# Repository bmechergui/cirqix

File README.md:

# Cirqix.ai — AI PCB Design Agent

> **From idea to manufacturable PCB, autonomously**

Cirqix is a cloud SaaS for PCB design powered by natural language. Describe your circuit, the AI agent generates a DRC-clean PCB and exports Gerbers/BOM for review and manual manufacturer submission.

---

## What it does

```
User prompt → 8 AI Agents → Schematic → ERC → Footprints → PCB → Placement → Routing → DRC → Gerbers/BOM
```

1. **Describe** — type your circuit in natural language
2. **Design** — 8 specialized AI agents create schematic, resolve footprints, place components, route traces, fix all DRC violations
3. **Review** — visualize schematic + PCB in KiCanvas, inspect in 3D, run SPICE simulation
4. **Manufacture** — download and review Gerbers/BOM, then submit them manually to JLCPCB

---

## Tech Stack

| Layer | Technology |
|-------|-----------|
| Frontend | Next.js 15 · Tailwind CSS · shadcn/ui · Zustand |
| Backend | Next.js API Routes |
| AI Agents | Claude SDK — Sonnet 4.6 (orchestrator) + 8× Haiku 4.5 (specialists) |
| PCB Engine | Circuit-Synth (Python pip) → native `.kicad_sch` + `.kicad_pcb` |
| KiCad Service | FastAPI · pcbnew · Freerouting · kicad-cli · ngspice · Docker |
| Database | Supabase · PostgreSQL · pgvector (footprint embeddings) |
| Queue | Redis · BullMQ (10 concurrent PCBs) |
| Viewer Schematic + PCB | KiCanvas (native `.kicad_sch` / `.kicad_pcb` from Supabase Storage) |
| Viewer 3D | Three.js + STEP via occt-import-js (Pro plan+) |
| SPICE Simulation | ngspice batch → parsed waveforms → Recharts (Pro plan+) |
| Auth | Supabase Auth (email + Google OAuth) |
| Payments | Lemon Squeezy |
| Infra | Vercel (frontend) · Railway (api) · DigitalOcean (KiCad service) |

---

## Monorepo Structure

```
cirqix/
├── apps/
│   └── web/                          # Next.js 15 app — port 3333
│       ├── src/app/
│       │   ├── (marketing)/          # cirqix.ai — landing, pricing, waitlist
│       │   ├── (workspace)/          # cirqix.ai/dashboard — auth required
│       │   └── api/                  # API Routes: /agent (SSE), /jlcpcb/order, /webhooks
│       ├── src/features/             # FSD: auth, chat-agent, credits, dashboard, marketing
│       ├── src/widgets/viewer/       # KiCanvas viewer (schematic + PCB) + Three.js 3D
│       ├── src/entities/             # project, pcb, credits
│       ├── src/shared/               # ui (shadcn), store (Zustand), lib, types
│       └── src/middleware.ts         # Supabase Auth JWT — protects /dashboard/*
├── packages/
│   ├── agents/                       # Claude SDK — orchestrator + 8 specialists + engines
│   │   └── src/engines/              # schematic-engine · placement-service · routing-service
│   │                                 # drc-service · export-service · footprint-service
│   ├── types/                        # @cirqix/types — single source of truth
│   ├── db/                           # Supabase client + migrations
│   ├── logger/                       # Pino logger
│   ├── utils/                        # cn() helpers
│   ├── ui/                           # Shared shadcn/ui components
│   ├── config-typescript/            # Shared strict tsconfig
│   └── config-eslint/                # Shared ESLint config
├── services/
│   └── kicad/                        # FastAPI + Circuit-Synth + pcbnew + Freerouting (Docker)
│       └── routers/                  # kicad_gen · placement · routing · drc · export · erc · simulation
├── docs/                             # Architecture, design system, agent prompts
├── PLAN.md                           # Full implementation plan (6 phases)
└── CLAUDE.md                         # AI assistant context & rules
```

---

## Getting Started

### Prerequisites

- Node.js ≥ 20
- pnpm ≥ 9 — **required** (`npm install` breaks the workspace)
- Docker (for KiCad service)

```bash
npm install -g pnpm   # install pnpm if needed
```

### Install

```bash
git clone https://github.com/bmechergui/cirqix.git
cd cirqix
pnpm install          # always use pnpm — never npm install
```

### Environment Variables

Copy `.env.example` and fill in the values:

```bash
cp .env.example apps/web/.env.local
```

Required variables:

```env
ANTHROPIC_API_KEY=
NEXT_PUBLIC_SUPABASE_URL=
NEXT_PUBLIC_SUPABASE_ANON_KEY=
SUPABASE_SERVICE_KEY=
REDIS_URL=
LEMON_SQUEEZY_API_KEY=
KICAD_SERVICE_URL=http://localhost:8766
KICAD_SERVICE_TOKEN=

# Agent mode: 'simulator' (no API calls) or 'orchestrator' (real Claude + Circuit-Synth)
CIRQIX_AGENT_MODE=orchestrator
```

### Dev

```bash
# Start all apps (Turborepo)
pnpm dev

# apps/web → http://localhost:3333
```

### KiCad Service (Docker — WSL recommended on Windows)

```bash
cd services/kicad
docker compose up -d --build
# → http://localhost:8766/health
```

`KICAD_SERVICE_TOKEN` est obligatoire pour toutes les routes sauf `/health` et
doit avoir la même valeur dans l'application web et le conteneur. Générez une
valeur aléatoire longue, par exemple avec
`python -c "import secrets; print(secrets.token_urlsafe(48))"`.

Le service est strictement serveur-à-serveur : il n'expose pas CORS et
n'exécute plus de Python généré. En local, Docker publie le port uniquement sur
`127.0.0.1`. Pour un déploiement inter-hôtes, utilisez une URL HTTPS derrière
un proxy ou un réseau privé ; ne transmettez jamais le jeton depuis un navigateur.

---

## Agent Pipeline

**8 specialized agents** orchestrated by Claude Sonnet 4.6 (max 15 iterations per PCB):

```
User → Sonnet 4.6 (orchestrator)
  ① Schema Agent    (Haiku 4.5) — Circuit-Synth Python → .kicad_sch
  ② ERC Agent       (Haiku 4.5) — kicad-cli ERC, auto-fix loop
  ③ Footprint Agent (Haiku 4.5) — 4-step cascade per component ref
  ④ KiCad Agent     (Haiku 4.5) — .kicad_pcb from schema + footprints
  ⑤ Placement Agent (Haiku 4.5) — pcbnew SetPosition/SetOrientationDegrees
  ⑥ Routing Agent   (Haiku 4.5) — Freerouting .dsn → .ses → .kicad_pcb
  ⑦ DRC Agent       (Haiku 4.5) — kicad-cli DRC, auto-fix loop (max 3×)
  ⑧ Export Agent    (Haiku 4.5) — Gerbers + drill + CPL zip → Supabase Storage
```

**Footprint cascade** (stops at first success):
1. KiCad official libraries (instant, free)
2. pgvector community cache (instant, free)
3. LCSC / EasyEDA API (by LCSC part number)
4. AI generation by Haiku (3 credits)

**Token optimization:** KiCad blob content (`kicad_sch_content`, `kicad_pcb_content`, Gerbers) is stripped from Sonnet tool_result messages → **~70% token savings** (~0.25€ vs 0.86€ per run).

Target cost: **~0.12€ per complete PCB**.

---

## Credit System

| Action | Credits |
|--------|---------|
| Chat message | 0.5 |
| Schematic | 2 |
| Placement | 2 |
| Routing | 3 |
| DRC check | 1 |
| Export Gerbers | 1 |
| Footprint AI | 3 |
| 3D view | 1 |
| SPICE simulation | 3 |

| Plan       | Price      | Credits        | Max layers |
|------------|------------|----------------|------------|
| Free       | 0€         | 5 / day        | 2          |
| Pro        | 29€/mo     | 100 / month    | 4          |
| Pro Max    | 99€/mo     | 300 / month    | 8          |
| Enterprise | Custom     | Unlimited      | Unlimited  |

---

## Implementation Roadmap

- [x] **Phase 0** — Monorepo setup, DB schema, KiCad Docker, CI/CD
- [x] **Phase 1** — Landing page + waitlist (design system, mock data)
- [x] **Phase 2** — Auth + dashboard + Claude agent + SSE streaming + Circuit-Synth + KiCanvas viewer + credits
- [x] **Phase 3** — pcbnew placement + Freerouting routing + kicad-cli DRC + Gerbers/BOM export + footprint cascade (KiCad/pgvector/LCSC/SnapMagic/AI)
- [x] **Phase 4.1** — 3D viewer (Three.js + STEP/occt-import-js, Pro+)
- [x] **Phase 4.2** — SPICE simulation (ngspice batch + Recharts waveforms, Pro+)
- [x] **Phase 4.3** — fabrication preparation (Gerbers + BOM download, manual JLCPCB submission)
- [ ] **Phase 4.4** — Lemon Squeezy payments (webhooks + billing page + top-ups)
- [ ] **Phase 5** — Rate limiting + E2E tests + monitoring + launch

See [PLAN.md](./PLAN.md) for the full detailed plan.

---

## License

Private — All rights reserved © 2026 Cirqix Technologies

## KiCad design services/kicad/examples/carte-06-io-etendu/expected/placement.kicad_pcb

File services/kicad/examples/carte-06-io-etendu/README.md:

# carte-06-io-etendu

> **Version git** `61ebbae` (2026-09-07) — le schema, le board et ces chiffres viennent
> tous de ce commit. ⚠️ Un README recopie a la main derive de ses mesures des la
> premiere relance : celui-ci est GENERE par `scripts/readme_banc_driver.py`.

**1 dossier = 1 cas = 1 question.** Celle-ci : *la chaine tient-elle a 35 composants ?*

## Le circuit

> un STM32 pilotant huit LED et exposant deux connecteurs d extension

⚠️ **Le schema n'est pas genere par l'agent Haiku** : il est ecrit par le driver —
Claude Code joue son role, comme `run_pipeline.py` le prevoit (« ecrit par le
driver »). C'est le seul chemin qui n'appelle aucun modele, et il repond a un angle
mort du banc historique : ses huit cartes partent toutes de `circuit.json` FIGES,
aucune d'une description en langage naturel — la promesse du produit.

## Mesures

| | |
|---|---|
| composants | 35 |
| nets | 27 |
| surface | 80 x 60 mm (137 mm2 par composant) |
| **routage** | **100 %** |
| DRC du pipeline | `clean=True`, 13 violation(s) |
| **DRC du board livre** | **0 erreur(s)**, 13 violation(s) au total |
| types (board livre) | silk_edge_clearance:1 · silk_over_copper:2 · silk_overlap:9 · track_dangling:1 |
| **fabricable** | **oui** — aucune violation de severite `error` sur le board livre |
| fichiers exportes | 20 |
| duree du pipeline | 624 s |

Cuivre reellement pose sur le board livre :

| segments | vias | zones | empreintes |
|---|---|---|---|
| 242 | 43 | 3 | 35 |

⚠️ Ces quatre nombres sont comptes **dans le board**, pas rapportes par un
compteur de progression. Ce depot a paye trois fois la difference : un rapport DRC
vide lu « 0 erreur », des nets KiCad 10 comptes a zero, et un driver annoncant
« 0/16 route » sur un board portant 62 segments.

## Note de conception

35 composants autour d un LQFP-48 : les broches d E/S sont prises sur les QUATRE cotes du boitier, jamais groupees d un seul — c est ce qui avait plafonne la Nucleo a 68 %.

## Rejouer

```
python scripts/banc_driver_llm.py examples/carte-06-io-etendu
python scripts/readme_banc_driver.py examples/carte-06-io-etendu
```

⚠️ `examples/` n'est **pas monte** dans le conteneur : il est cuit dans l'image. Le
banc extrait donc `expected/final.kicad_pcb` aussitot, sans quoi l'artefact part au
premier redemarrage — la lecon des worktrees vides, transposee.

Artefacts : `expected/final.kicad_pcb`, `expected/journal.txt`,
`expected/mesures.json`.

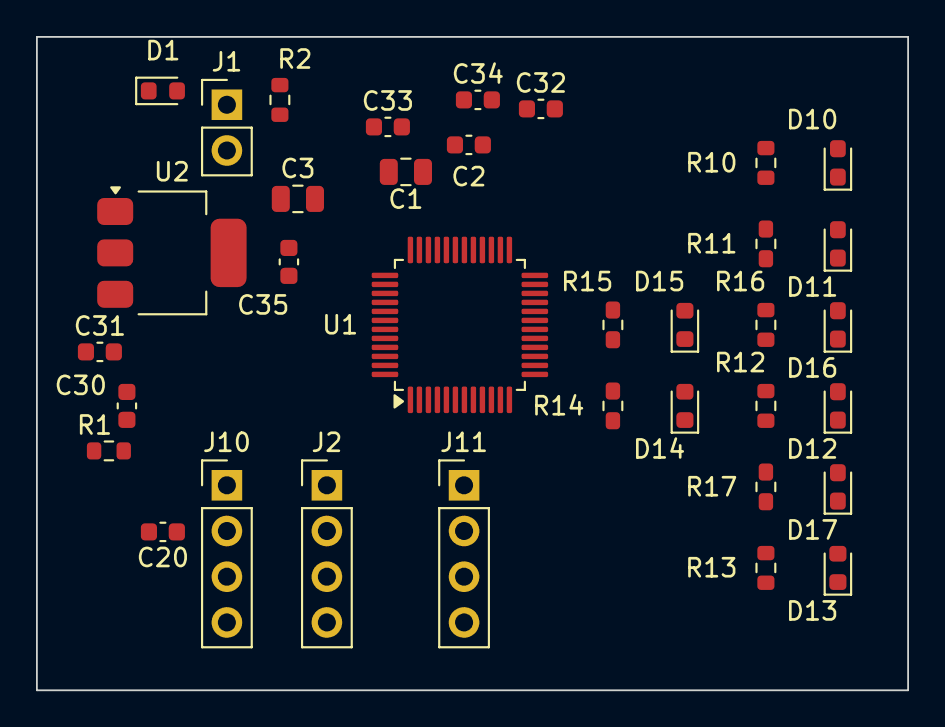
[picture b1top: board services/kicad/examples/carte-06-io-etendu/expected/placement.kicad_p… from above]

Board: 2 copper layers, 48.4 x 36.3 mm, 35 parts (0 on the bottom side), 27 nets, no tracks yet.

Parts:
C1, C3: 10uF; C_0805_2012Metric
C2, C20, C30, C31, C32, C33, C34, C35: 100nF; C_0603_1608Metric
D1: PWR; LED_0603_1608Metric
D10, D11, D12, D13, D14, D15, D16, D17: LED; LED_0603_1608Metric
J1: IN_5V; PinHeader_1x02_P2.54mm_Vertical
J2: SWD; PinHeader_1x04_P2.54mm_Vertical
J10: IO0; PinHeader_1x04_P2.54mm_Vertical
J11: IO1; PinHeader_1x04_P2.54mm_Vertical
R1, R10, R11, R12, R13, R14, R15, R16, R17: 1k; R_0603_1608Metric
R2: 10k; R_0603_1608Metric
U1: STM32F103C8T6; LQFP-48_7x7mm_P0.5mm
U2: AMS1117-3.3; SOT-223-3_TabPin2

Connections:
+3V3: C3.1, C30.1, C31.1, C32.1, C33.1, C34.1, C35.1, J2.1, J10.3, J11.3, R1.1, R2.2, U1.1, U1.24, U1.36, U1.48, U2.2
EXT0_1: J10.1, U1.12
EXT0_2: J10.2, U1.13
EXT1_1: J11.1, U1.14
EXT1_2: J11.2, U1.15
GND: C1.2, C2.2, C3.2, C20.2, C30.2, C31.2, C32.2, C33.2, C34.2, C35.2, D1.1, D10.1, D11.1, D12.1, D13.1, D14.1, D15.1, D16.1, D17.1, J1.2, J10.4, J11.4, U1.8, U1.23, U1.35, U1.47, U2.1
IO_L0: R10.1, U1.2
IO_L1: R11.1, U1.3
IO_L2: R12.1, U1.4
IO_L3: R13.1, U1.5
IO_L4: R14.1, U1.6
IO_L5: R15.1, U1.9
IO_L6: R16.1, U1.10
IO_L7: R17.1, U1.11
LEDA0: D10.2, R10.2
LEDA1: D11.2, R11.2
LEDA2: D12.2, R12.2
LEDA3: D13.2, R13.2
LEDA4: D14.2, R14.2
LEDA5: D15.2, R15.2
LEDA6: D16.2, R16.2
LEDA7: D17.2, R17.2
LED_PWR: D1.2, R1.2
NRST: C20.1, J2.4, R2.1, U1.7
SWCLK: J2.3, U1.37
SWDIO: J2.2, U1.34
VIN: C1.1, C2.1, J1.1, U2.3

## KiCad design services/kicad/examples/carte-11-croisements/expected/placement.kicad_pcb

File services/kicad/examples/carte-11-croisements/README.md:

# carte-11-croisements

> **Version git** `1c708ea` (2026-09-07) — le schema, le board et ces chiffres viennent
> tous de ce commit. ⚠️ Un README recopie a la main derive de ses mesures des la
> premiere relance : celui-ci est GENERE par `scripts/readme_banc_driver.py`.

**1 dossier = 1 cas = 1 question.** Celle-ci : *la chaine tient-elle a 6 composants ?*

## Le circuit

> deux connecteurs 2x20 face a face, relies par un faisceau de 32 signaux cable EN ORDRE INVERSE — chaque liaison croise toutes les autres.

⚠️ **Le schema n'est pas genere par l'agent Haiku** : il est ecrit par le driver —
Claude Code joue son role, comme `run_pipeline.py` le prevoit (« ecrit par le
driver »). C'est le seul chemin qui n'appelle aucun modele, et il repond a un angle
mort du banc historique : ses huit cartes partent toutes de `circuit.json` FIGES,
aucune d'une description en langage naturel — la promesse du produit.

## Mesures

| | |
|---|---|
| composants | 6 |
| nets | 34 |
| surface | 90 x 60 mm (900 mm2 par composant) |
| **routage** | **3 %** |
| DRC du pipeline | `clean=False`, 104 violation(s) |
| **DRC du board livre** | **42 erreur(s)**, 55 violation(s) au total |
| types (board livre) | copper_edge_clearance:2 · hole_to_hole:4 · silk_edge_clearance:2 · silk_overlap:1 · track_dangling:4 · unconnected_items:40 · via_dangling:2 |
| **fabricable** | **NON** — 42 erreur(s) : copper_edge_clearance, unconnected_items |
| fichiers exportes | 20 |
| duree du pipeline | 521 s |

Cuivre reellement pose sur le board livre :

| segments | vias | zones | empreintes |
|---|---|---|---|
| 13 | 3 | 0 | 6 |

⚠️ Ces quatre nombres sont comptes **dans le board**, pas rapportes par un
compteur de progression. Ce depot a paye trois fois la difference : un rapport DRC
vide lu « 0 erreur », des nets KiCad 10 comptes a zero, et un driver annoncant
« 0/16 route » sur un board portant 62 segments.

## Note de conception

6 composants sur 90 x 60 mm. La densite n est PAS le sujet : cette carte est peu peuplee et route pourtant mal sur deux couches.

⚠️ ELLE EXISTE POUR METTRE L ESCALADE DE COUCHES A L EPREUVE. Aucune carte de ce depot n avait jamais declenche le passage a 4 couches — non parce que le mecanisme serait casse, mais parce qu aucune n en avait besoin : meme `stm32-100`, que `_couches_pour_echapper` declare a 4 couches, route a 100 % sur DEUX en 208 s. L absence de besoin n est pas une preuve de bon fonctionnement.

Ce qui rend deux couches insuffisantes ici n est pas le nombre de pistes mais leur NON-PLANARITE : un faisceau inverse de N signaux impose ~N²/2 croisements, et sur deux couches la face arriere porte le plan de masse — il ne reste qu UNE face de signal. Deux pistes qui se croisent ne tiennent pas sur une meme face.

Resultat attendu : echec net a 2 couches, puis passage a 4.

## Rejouer

```
python scripts/banc_driver_llm.py examples/carte-11-croisements
python scripts/readme_banc_driver.py examples/carte-11-croisements
```

⚠️ `examples/` n'est **pas monte** dans le conteneur : il est cuit dans l'image. Le
banc extrait donc `expected/final.kicad_pcb` aussitot, sans quoi l'artefact part au
premier redemarrage — la lecon des worktrees vides, transposee.

Artefacts : `expected/final.kicad_pcb`, `expected/journal.txt`,
`expected/mesures.json`.

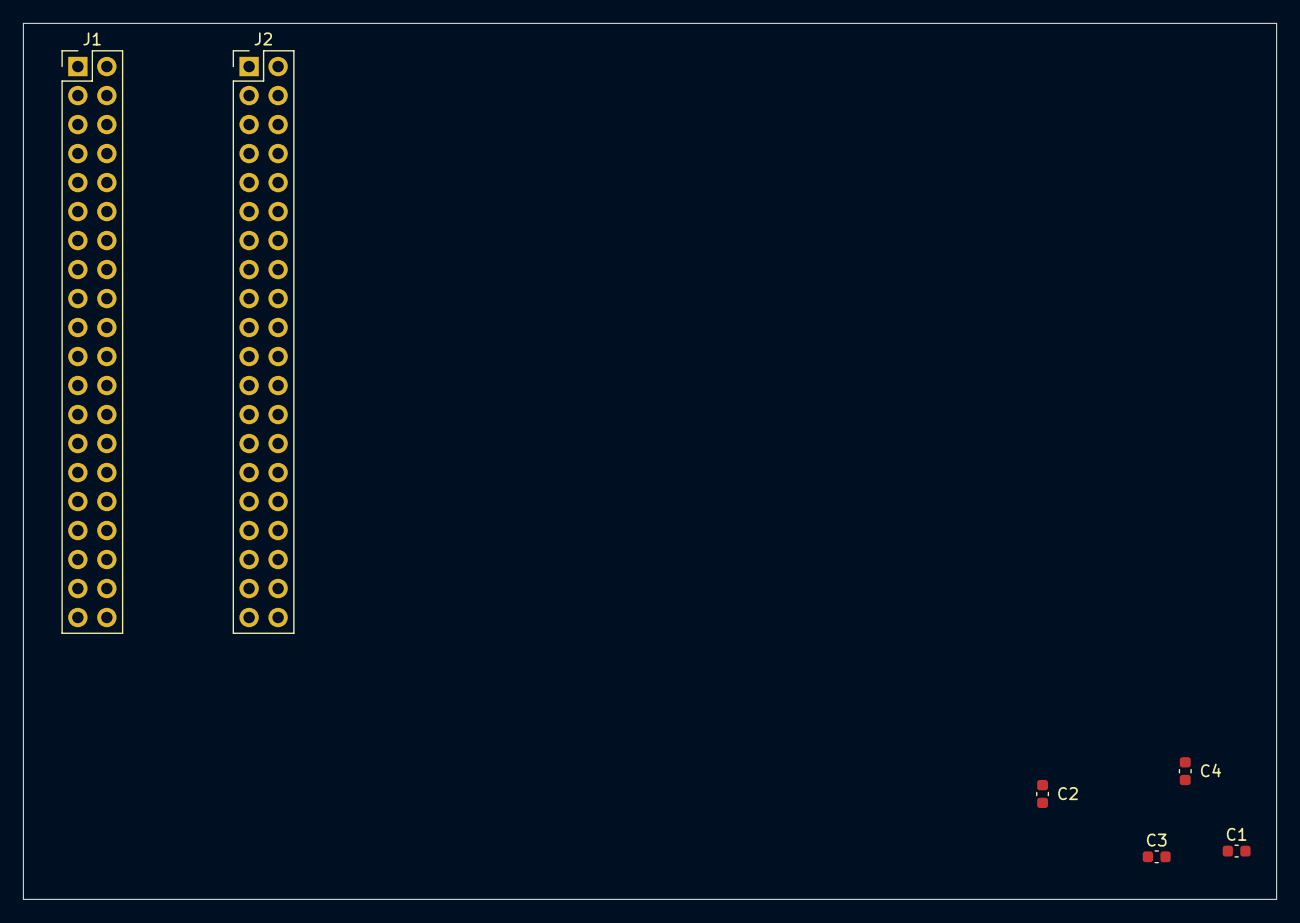
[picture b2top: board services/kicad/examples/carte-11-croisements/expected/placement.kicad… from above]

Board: 2 copper layers, 109.8 x 76.7 mm, 6 parts (0 on the bottom side), 34 nets, no tracks yet.

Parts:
C1, C2, C3, C4: 100nF; C_0603_1608Metric
J1: BUS_A; PinHeader_2x20_P2.54mm_Vertical
J2: BUS_B; PinHeader_2x20_P2.54mm_Vertical

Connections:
+3V3: C1.1, C2.1, C3.1, C4.1, J1.34, J2.34
GND: C1.2, C2.2, C3.2, C4.2, J1.33, J2.33
X01: J1.1, J2.32
X02: J1.2, J2.31
X03: J1.3, J2.30
X04: J1.4, J2.29
X05: J1.5, J2.28
X06: J1.6, J2.27
X07: J1.7, J2.26
X08: J1.8, J2.25
X09: J1.9, J2.24
X10: J1.10, J2.23
X11: J1.11, J2.22
X12: J1.12, J2.21
X13: J1.13, J2.20
X14: J1.14, J2.19
X15: J1.15, J2.18
X16: J1.16, J2.17
X17: J1.17, J2.16
X18: J1.18, J2.15
X19: J1.19, J2.14
X20: J1.20, J2.13
X21: J1.21, J2.12
X22: J1.22, J2.11
X23: J1.23, J2.10
X24: J1.24, J2.9
X25: J1.25, J2.8
X26: J1.26, J2.7
X27: J1.27, J2.6
X28: J1.28, J2.5
X29: J1.29, J2.4
X30: J1.30, J2.3
X31: J1.31, J2.2
X32: J1.32, J2.1

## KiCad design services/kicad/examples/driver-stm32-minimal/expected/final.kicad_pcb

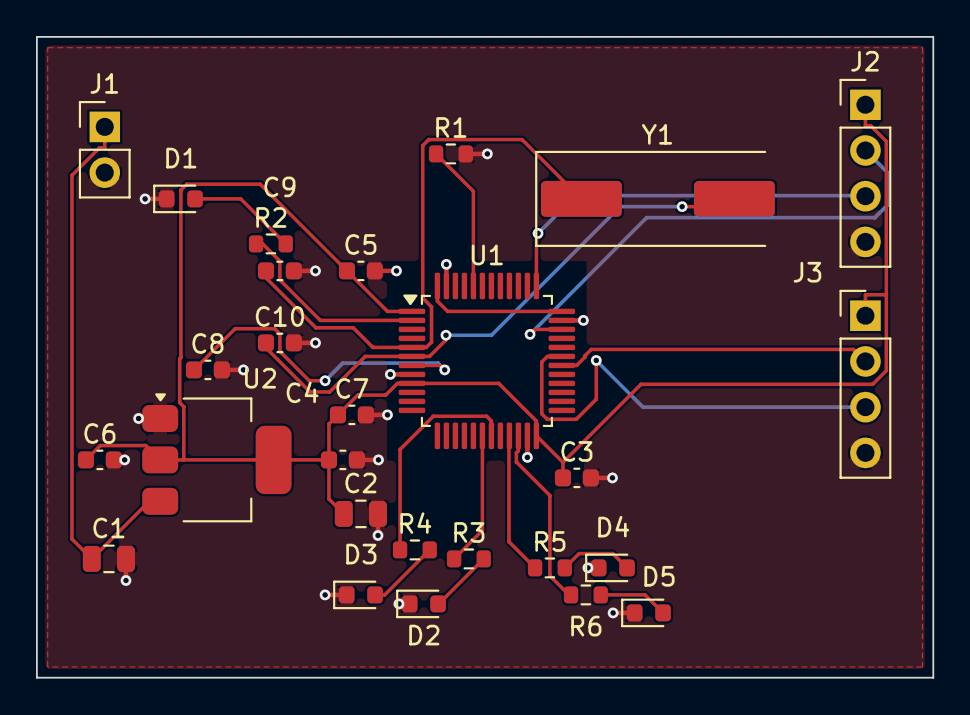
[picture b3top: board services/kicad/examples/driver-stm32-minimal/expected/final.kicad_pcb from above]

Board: 2 copper layers, 49.8 x 35.6 mm, 27 parts (0 on the bottom side), 22 nets.

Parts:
C1, C2: 10uF; C_0805_2012Metric
C3, C4, C5, C6, C7, C8: 100nF; C_0603_1608Metric
C9, C10: 20pF; C_0603_1608Metric
D1: LED_GREEN; LED_0603_1608Metric
D2, D3, D4, D5: LED_RED; LED_0603_1608Metric
J1: PWR_5V; PinHeader_1x02_P2.54mm_Vertical
J2: SWD; PinHeader_1x04_P2.54mm_Vertical
J3: UART1; PinHeader_1x04_P2.54mm_Vertical
R1: 10k; R_0603_1608Metric
R2, R3, R4, R5, R6: 470R; R_0603_1608Metric
U1: STM32F103C8T6; LQFP-48_7x7mm_P0.5mm
U2: AMS1117-3.3; SOT-223-3_TabPin2
Y1: 8MHz; Crystal_SMD_HC49-SD

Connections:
+3V3: C2.1, C3.1, C4.1, C5.1, C6.1, C7.1, J2.1, J3.1, U1.1, U1.9, U1.24, U2.2
+5V: C1.1, J1.1, U2.3
BOOT0: R1.1, U1.44
D1_A: D1.2, R2.2
D2_A: D2.2, R3.2
D3_A: D3.2, R4.2
D4_A: D4.2, R5.2
D5_A: D5.2, R6.2
GND: C1.2, C2.2, C3.2, C4.2, C5.2, C6.2, C7.2, C8.2, C9.2, C10.2, D1.1, D2.1, D3.1, D4.1, D5.1, J1.2, J2.4, J3.4, R1.2, U1.8, U1.23, U1.35, U1.47, U2.1
LED_PB0: R3.1, U1.18
LED_PB1: R4.1, U1.19
LED_PB10: R5.1, U1.21
LED_PB11: R6.1, U1.22
LED_PC13: R2.1, U1.2
NRST: C8.1, U1.7
OSC_IN: C9.1, U1.5, Y1.1
OSC_OUT: C10.1, U1.6, Y1.2
PWR_FLAG: U1.36, U1.48
SWCLK: J2.3, U1.37
SWDIO: J2.2, U1.34
UART1_RX: J3.3, U1.31
UART1_TX: J3.2, U1.30

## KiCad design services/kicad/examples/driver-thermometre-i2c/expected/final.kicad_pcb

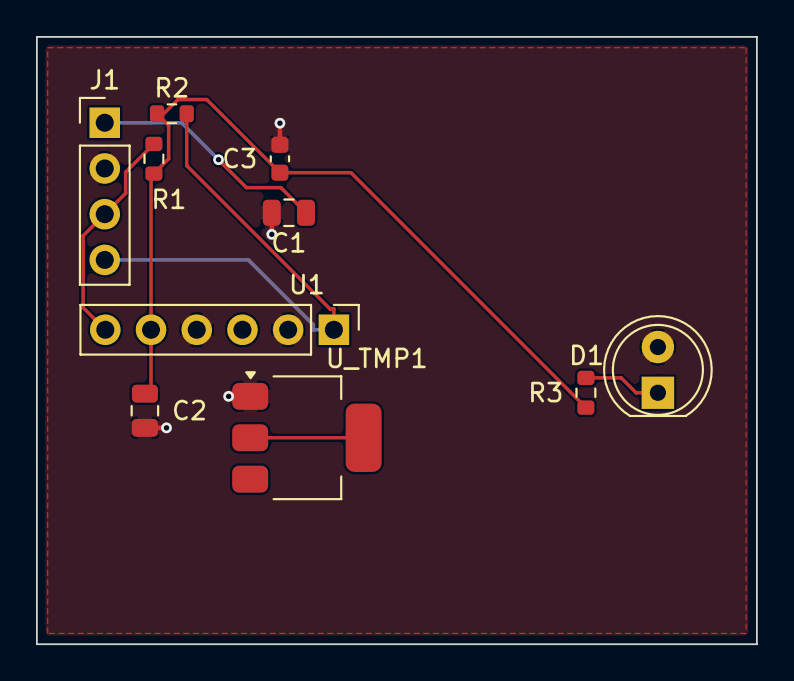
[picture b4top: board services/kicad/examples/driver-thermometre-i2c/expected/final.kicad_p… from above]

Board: 2 copper layers, 40.0 x 33.7 mm, 10 parts (0 on the bottom side), 6 nets.

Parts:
C1, C2: 10uF; C_0805_2012Metric
C3: 100nF; C_0603_1608Metric
D1: LED_GREEN; LED_D5.0mm
J1: 5V_GND_SDA_SCL; PinHeader_1x04_P2.54mm_Vertical
R1, R2: 4.7k; R_0603_1608Metric
R3: 1k; R_0603_1608Metric
U1: AMS1117-3.3; SOT-223-3_TabPin2
U_TMP1: TMP102; PinHeader_1x06_P2.54mm_Vertical

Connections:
+3V3: C2.1, C3.1, R1.1, R2.1, R3.1, U_TMP1.5
+5V: C1.1, J1.1
GND: C1.2, C2.2, C3.2, D1.2, J1.2, U1.1, U_TMP1.2, U_TMP1.4
NET_R3_D1: D1.1, R3.2
SCL: J1.4, R2.2, U_TMP1.1
SDA: J1.3, R1.2, U_TMP1.6

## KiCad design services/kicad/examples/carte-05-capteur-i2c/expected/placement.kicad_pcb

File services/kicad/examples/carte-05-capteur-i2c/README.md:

# carte-05-capteur-i2c

> **Version git** `e74648b` (2026-09-07) — le schema, le board et ces chiffres viennent
> tous de ce commit. ⚠️ Un README recopie a la main derive de ses mesures des la
> premiere relance : celui-ci est GENERE par `scripts/readme_banc_driver.py`.

**1 dossier = 1 cas = 1 question.** Celle-ci : *la chaine tient-elle a 26 composants ?*

## Le circuit

> un STM32 avec un capteur BME280 en I2C, deux LED d etat et un connecteur d extension

⚠️ **Le schema n'est pas genere par l'agent Haiku** : il est ecrit par le driver —
Claude Code joue son role, comme `run_pipeline.py` le prevoit (« ecrit par le
driver »). C'est le seul chemin qui n'appelle aucun modele, et il repond a un angle
mort du banc historique : ses huit cartes partent toutes de `circuit.json` FIGES,
aucune d'une description en langage naturel — la promesse du produit.

## Mesures

| | |
|---|---|
| composants | 26 |
| nets | 13 |
| surface | 70 x 50 mm (135 mm2 par composant) |
| **routage** | **100 %** |
| DRC du pipeline | `clean=False`, 43 violation(s) |
| **DRC du board livre** | **5 erreur(s)**, 30 violation(s) au total |
| types (board livre) | invalid_outline:1 · item_on_disabled_layer:4 · silk_over_copper:10 · silk_overlap:3 · track_dangling:10 · via_dangling:2 |
| **fabricable** | **NON** — 5 erreur(s) : invalid_outline, item_on_disabled_layer |
| fichiers exportes | 27 |
| duree du pipeline | 1052 s |

Cuivre reellement pose sur le board livre :

| segments | vias | zones | empreintes |
|---|---|---|---|
| 290 | 29 | 0 | 26 |

⚠️ Ces quatre nombres sont comptes **dans le board**, pas rapportes par un
compteur de progression. Ce depot a paye trois fois la difference : un rapport DRC
vide lu « 0 erreur », des nets KiCad 10 comptes a zero, et un driver annoncant
« 0/16 route » sur un board portant 62 segments.

## Note de conception

30 composants : 70 x 50 mm. Le bus I2C sort du LQFP-48 par le bas, ses tirages sont groupes pres du capteur.

## Rejouer

```
python scripts/banc_driver_llm.py examples/carte-05-capteur-i2c
python scripts/readme_banc_driver.py examples/carte-05-capteur-i2c
```

⚠️ `examples/` n'est **pas monte** dans le conteneur : il est cuit dans l'image. Le
banc extrait donc `expected/final.kicad_pcb` aussitot, sans quoi l'artefact part au
premier redemarrage — la lecon des worktrees vides, transposee.

Artefacts : `expected/final.kicad_pcb`, `expected/journal.txt`,
`expected/mesures.json`.

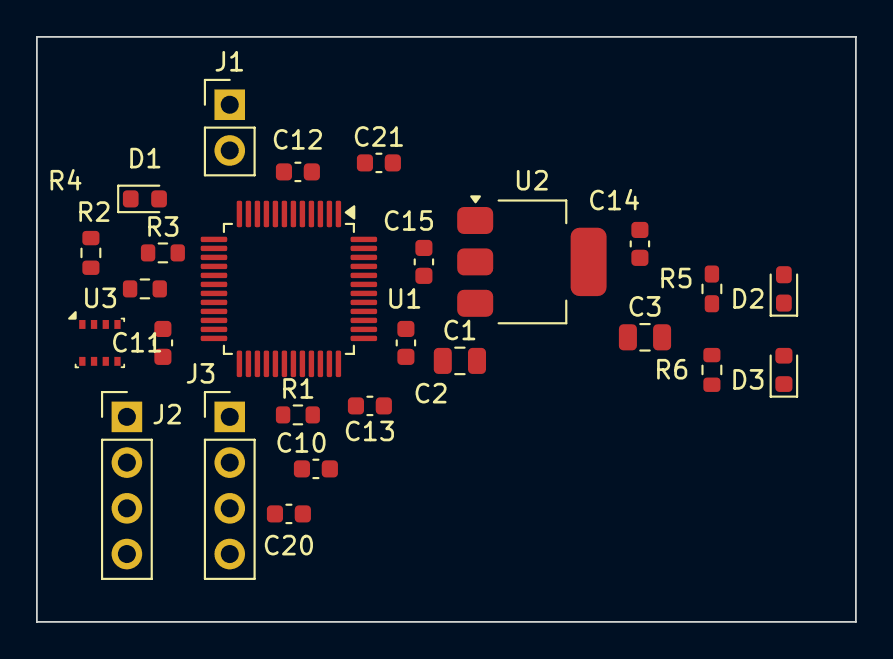
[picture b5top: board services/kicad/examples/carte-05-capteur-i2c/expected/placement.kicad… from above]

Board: 2 copper layers, 45.5 x 32.5 mm, 26 parts (0 on the bottom side), 13 nets, no tracks yet.

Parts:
C1, C3: 10uF; C_0805_2012Metric
C2, C10, C11, C12, C13, C14, C15, C20, C21: 100nF; C_0603_1608Metric
D1: PWR; LED_0603_1608Metric
D2: ST1; LED_0603_1608Metric
D3: ST2; LED_0603_1608Metric
J1: IN_5V; PinHeader_1x02_P2.54mm_Vertical
J2: SWD; PinHeader_1x04_P2.54mm_Vertical
J3: I2C; PinHeader_1x04_P2.54mm_Vertical
R1, R5, R6: 1k; R_0603_1608Metric
R2: 10k; R_0603_1608Metric
R3, R4: 4k7; R_0603_1608Metric
U1: STM32F103C8T6; LQFP-48_7x7mm_P0.5mm
U2: AMS1117-3.3; SOT-223-3_TabPin2
U3: BME280; Bosch_LGA-8_2.5x2.5mm_P0.65mm_ClockwisePinNumbering

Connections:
+3V3: C3.1, C10.1, C11.1, C12.1, C13.1, C14.1, C15.1, C21.1, J2.1, J3.3, R1.1, R2.2, R3.1, R4.1, U1.1, U1.24, U1.36, U1.48, U2.2, U3.1
GND: C1.2, C2.2, C3.2, C10.2, C11.2, C12.2, C13.2, C14.2, C15.2, C20.2, C21.2, D1.1, D2.1, D3.1, J1.2, J3.4, U1.8, U1.23, U1.35, U1.47, U2.1, U3.2, U3.7
IO_ST1: R5.1, U1.14
IO_ST2: R6.1, U1.15
LED1_A: D2.2, R5.2
LED2_A: D3.2, R6.2
LED_PWR: D1.2, R1.2
NRST: C20.1, J2.4, R2.1, U1.7
SCL: J3.1, R3.2, U1.21, U3.4
SDA: J3.2, R4.2, U1.22, U3.6
SWCLK: J2.3, U1.37
SWDIO: J2.2, U1.34
VIN: C1.1, C2.1, J1.1, U2.3
